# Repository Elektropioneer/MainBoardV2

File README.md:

# Electropioneer Main Board 
This repo is dedicated to developing the new Main Board for the Electropioneer team
## Software
We are using KiCAD to develop the PCB

## Protection from reverse current
We are using the simplest way to protect out circuits, a P-Channel MOSFET.
The MOSFET won't turn on when the voltage on the gate is above 0 (exact voltage defined in the datasheet)

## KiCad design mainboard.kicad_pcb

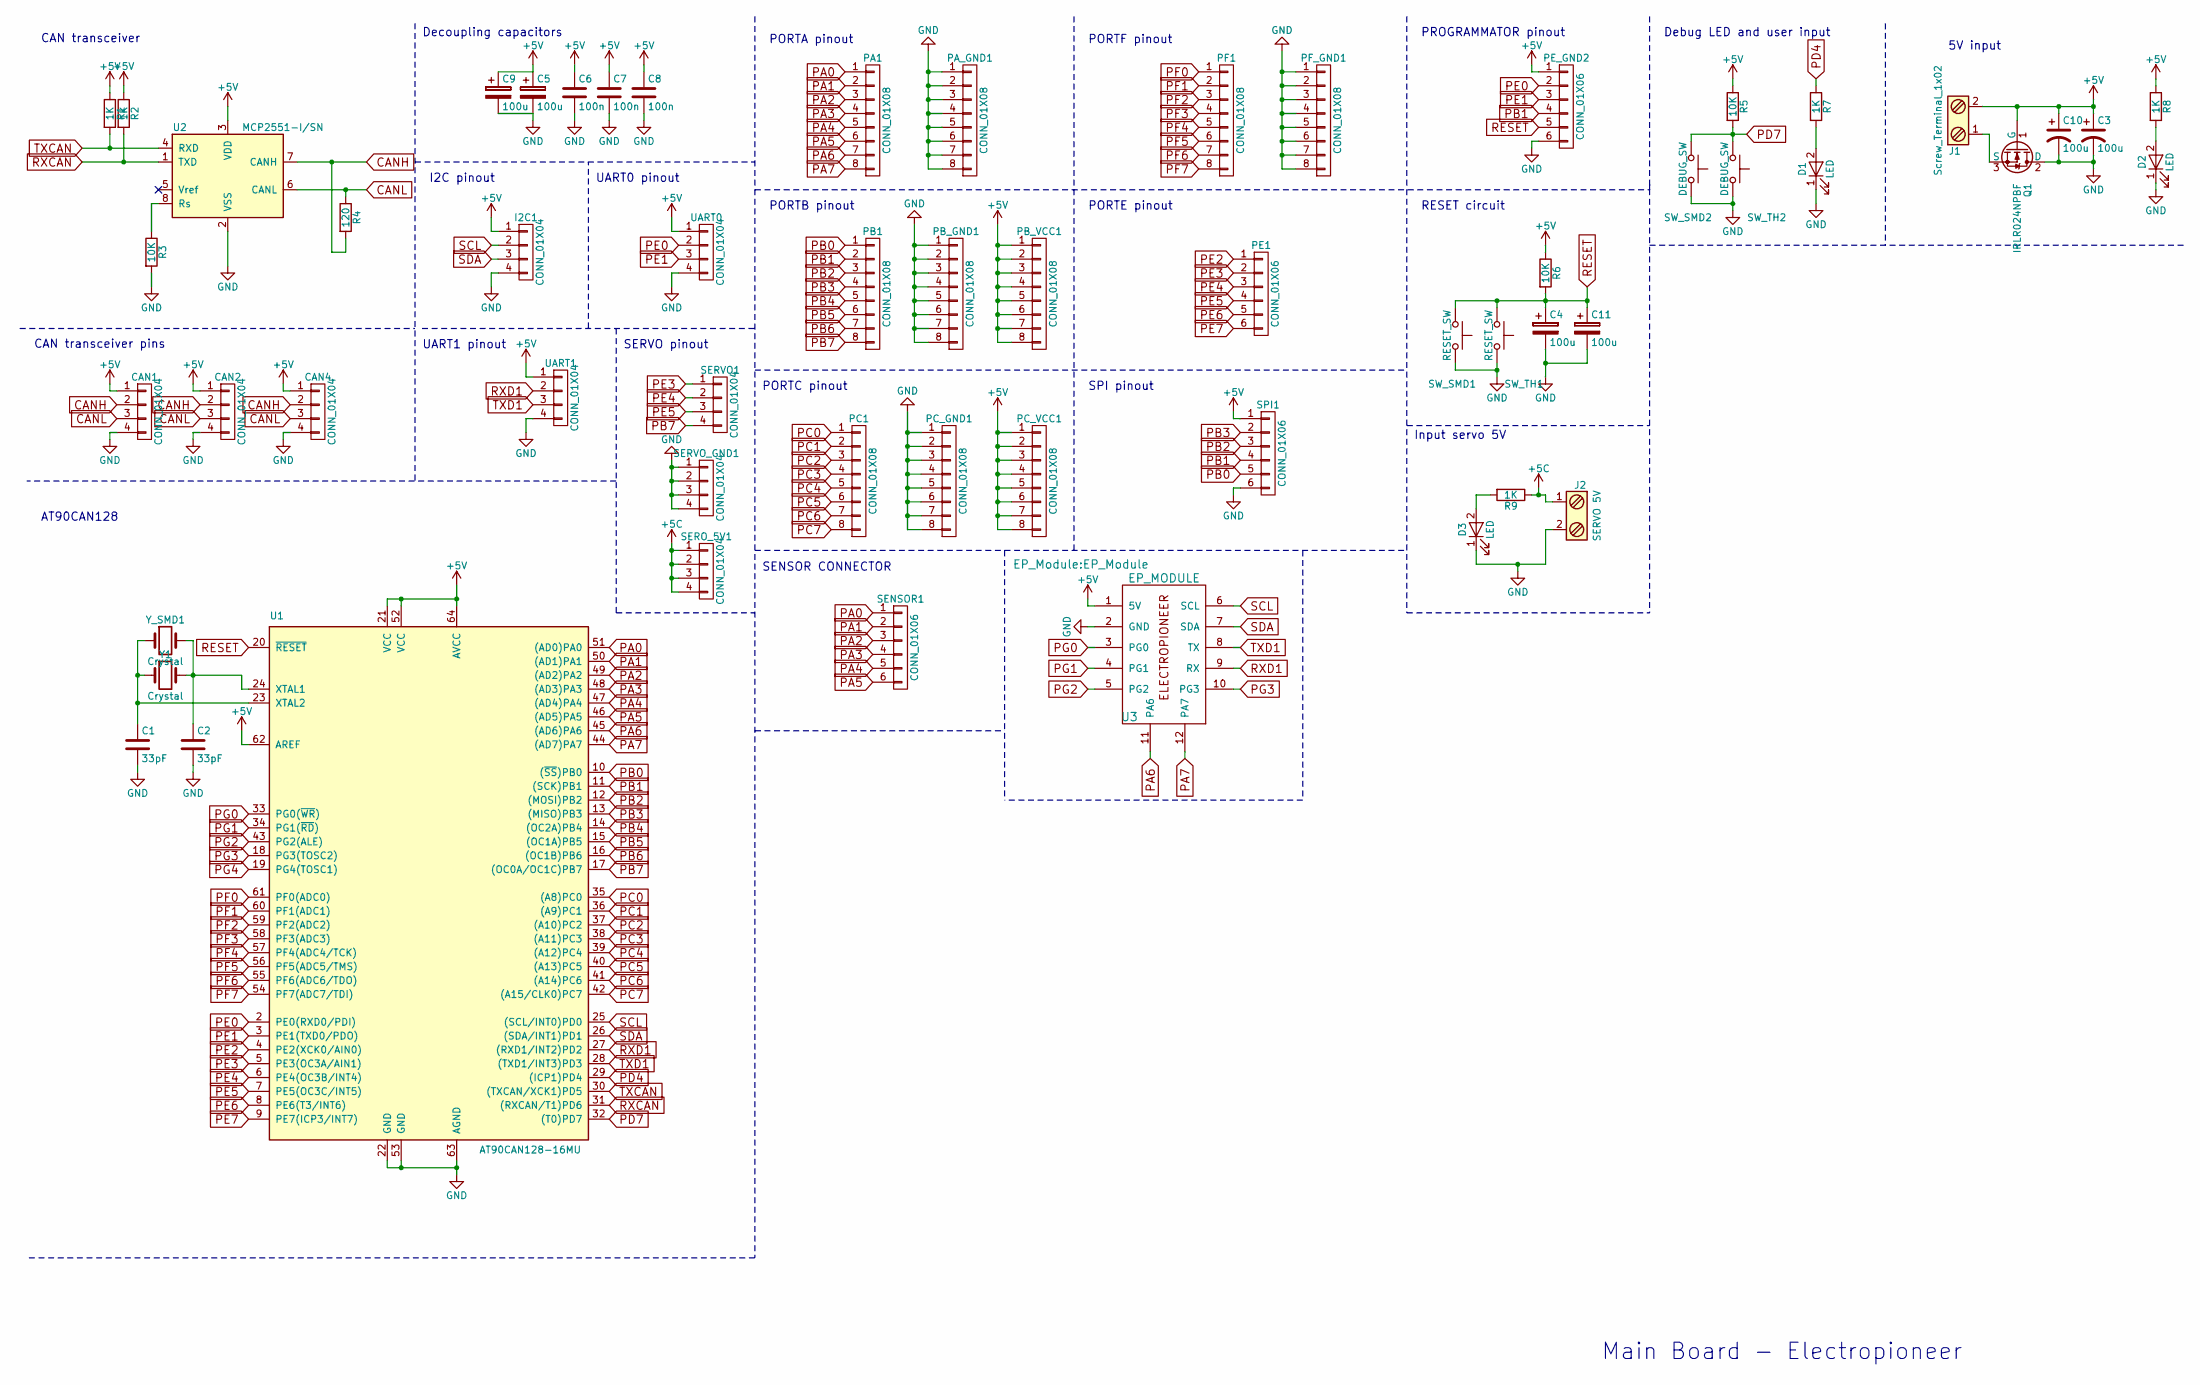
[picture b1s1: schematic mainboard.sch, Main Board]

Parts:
C1, C2: 33pF; C_0805
C3, C4, C5: 100u; CP_Elec_6.3x4.5
C6, C7, C8: 100n; C_0805
C9, C10, C11: 100u; CP_Radial_D7.5mm_P2.50mm
CAN1, CAN2, CAN4: CONN_01X04; Pin_Header_Straight_1x04_Pitch2.54mm
D1, D2, D3: LED; LED_0805
I2C1: CONN_01X04; Pin_Header_Straight_1x04_Pitch2.54mm
J1: Screw_Terminal_1x02; TerminalBlock_Pheonix_MPT-2.54mm_2pol
J2: SERVO 5V; TerminalBlock_Pheonix_MPT-2.54mm_2pol
PA1: CONN_01X08; Pin_Header_Straight_1x08_Pitch2.54mm
PA_GND1: CONN_01X08; Pin_Header_Straight_1x08_Pitch2.54mm
PB1: CONN_01X08; Pin_Header_Straight_1x08_Pitch2.54mm
PB_GND1: CONN_01X08; Pin_Header_Straight_1x08_Pitch2.54mm
PB_VCC1: CONN_01X08; Pin_Header_Straight_1x08_Pitch2.54mm
PC1: CONN_01X08; Pin_Header_Straight_1x08_Pitch2.54mm
PC_GND1: CONN_01X08; Pin_Header_Straight_1x08_Pitch2.54mm
PC_VCC1: CONN_01X08; Pin_Header_Straight_1x08_Pitch2.54mm
PE1: CONN_01X06; Pin_Header_Straight_1x06_Pitch2.54mm
PE_GND2: CONN_01X06; Pin_Header_Straight_1x06_Pitch2.54mm
PF1: CONN_01X08; Pin_Header_Straight_1x08_Pitch2.54mm
PF_GND1: CONN_01X08; Pin_Header_Straight_1x08_Pitch2.54mm
Q1: IRLR024NPBF; TO-252-2
R1, R2, R7, R8, R9: 1K; R_0805
R3, R5: 10K; R_0805
R4: 120; R_0805
R6: 10K; R_1206
SENSOR1: CONN_01X06; Pin_Header_Straight_1x06_Pitch2.54mm
SERO_5V1: CONN_01X04; Pin_Header_Straight_1x04_Pitch2.54mm
SERVO1: CONN_01X04; Pin_Header_Straight_1x04_Pitch2.54mm
SERVO_GND1: CONN_01X04; Pin_Header_Straight_1x04_Pitch2.54mm
SPI1: CONN_01X06; Pin_Header_Straight_1x06_Pitch2.54mm
SW_SMD1: RESET_SW; SW_DIP_x1_W7.62mm_Slide_Copal_CHS-B
SW_SMD2: DEBUG_SW; SW_DIP_x1_W7.62mm_Slide_Copal_CHS-B
SW_TH1: RESET_SW; SW_PUSH_6mm
SW_TH2: DEBUG_SW; SW_PUSH_6mm
U1: AT90CAN128-16MU; TQFP-64_14x14mm_Pitch0.8mm
U2: MCP2551-I/SN; SOIC-8_3.9x4.9mm_Pitch1.27mm
U3: EP_MODULE; EP_Module
UART0, UART1: CONN_01X04; Pin_Header_Straight_1x04_Pitch2.54mm
Y1: Crystal; Crystal_HC18-U_Vertical
Y_SMD1: Crystal; Crystal_SMD_HC49-SD

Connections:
+5C: J2.1, R9.1, SERO_5V1.1, SERO_5V1.2, SERO_5V1.3, SERO_5V1.4
+5V: C3.1, C5.1, C6.1, C7.1, C8.1, C9.1, C10.1, CAN1.1, CAN2.1, CAN4.1, I2C1.1, J1.2, PB_VCC1.1, PB_VCC1.2, PB_VCC1.3, PB_VCC1.4, PB_VCC1.5, PB_VCC1.6, PB_VCC1.7, PB_VCC1.8, PC_VCC1.1, PC_VCC1.2, PC_VCC1.3, PC_VCC1.4, PC_VCC1.5, PC_VCC1.6, PC_VCC1.7, PC_VCC1.8, PE_GND2.1, Q1.1 (G), R1.1, R2.1, R5.1, R6.1, R8.1, SPI1.1, U1.21 (VCC), U1.52 (VCC), U1.62 (AREF), U1.64 (AVCC), U2.3 (VDD), U3.1 (5V), UART0.1, UART1.1
CANH: CAN1.2, CAN2.2, CAN4.2, R4.2, U2.7 (CANH)
CANL: CAN1.3, CAN2.3, CAN4.3, R4.1, U2.6 (CANL)
GND: C1.2, C2.2, C3.2, C4.2, C5.2, C6.2, C7.2, C8.2, C9.2, C10.2, C11.2, CAN1.4, CAN2.4, CAN4.4, D1.1 (K), D2.1 (K), D3.1 (K), I2C1.4, J2.2, PA_GND1.1, PA_GND1.2, PA_GND1.3, PA_GND1.4, PA_GND1.5, PA_GND1.6, PA_GND1.7, PA_GND1.8, PB_GND1.1, PB_GND1.2, PB_GND1.3, PB_GND1.4, PB_GND1.5, PB_GND1.6, PB_GND1.7, PB_GND1.8, PC_GND1.1, PC_GND1.2, PC_GND1.3, PC_GND1.4, PC_GND1.5, PC_GND1.6, PC_GND1.7, PC_GND1.8, PE_GND2.6, PF_GND1.1, PF_GND1.2, PF_GND1.3, PF_GND1.4, PF_GND1.5, PF_GND1.6, PF_GND1.7, PF_GND1.8, Q1.2 (D), R3.2, SERVO_GND1.1, SERVO_GND1.2, SERVO_GND1.3, SERVO_GND1.4, SPI1.6, SW_SMD1.2, SW_SMD2.2, SW_TH1.2, SW_TH2.2, U1.22 (GND), U1.53 (GND), U1.63 (AGND), U2.2 (VSS), U3.2 (GND), UART0.4, UART1.4
unnamed: C1.1, U1.23 (XTAL2), Y1.1, Y_SMD1.1
unnamed: C2.1, U1.24 (XTAL1), Y1.2, Y_SMD1.2
unnamed: D1.2 (A), R7.2
unnamed: D2.2 (A), R8.2
unnamed: D3.2 (A), R9.2
unnamed: J1.1, Q1.3 (S)
unnamed: R3.1, U2.8 (Rs)
PA0: PA1.1, SENSOR1.1, U1.51 ((AD0)PA0)
PA1: PA1.2, SENSOR1.2, U1.50 ((AD1)PA1)
PA2: PA1.3, SENSOR1.3, U1.49 ((AD2)PA2)
PA3: PA1.4, SENSOR1.4, U1.48 ((AD3)PA3)
PA4: PA1.5, SENSOR1.5, U1.47 ((AD4)PA4)
PA5: PA1.6, SENSOR1.6, U1.46 ((AD5)PA5)
PA6: PA1.7, U1.45 ((AD6)PA6), U3.11 (PA6)
PA7: PA1.8, U1.44 ((AD7)PA7), U3.12 (PA7)
PB0: PB1.1, SPI1.5, U1.10 ((~SS~)PB0)
PB1: PB1.2, PE_GND2.4, SPI1.4, U1.11 ((SCK)PB1)
PB2: PB1.3, SPI1.3, U1.12 ((MOSI)PB2)
PB3: PB1.4, SPI1.2, U1.13 ((MISO)PB3)
PB4: PB1.5, U1.14 ((OC2A)PB4)
PB5: PB1.6, U1.15 ((OC1A)PB5)
PB6: PB1.7, U1.16 ((OC1B)PB6)
PB7: PB1.8, SERVO1.4, U1.17 ((OC0A/OC1C)PB7)
PC0: PC1.1, U1.35 ((A8)PC0)
PC1: PC1.2, U1.36 ((A9)PC1)
PC2: PC1.3, U1.37 ((A10)PC2)
PC3: PC1.4, U1.38 ((A11)PC3)
PC4: PC1.5, U1.39 ((A12)PC4)
PC5: PC1.6, U1.40 ((A13)PC5)
PC6: PC1.7, U1.41 ((A14)PC6)
PC7: PC1.8, U1.42 ((A15/CLK0)PC7)
PD4: R7.1, U1.29 ((ICP1)PD4)
PD7: R5.2, SW_SMD2.1, SW_TH2.1, U1.32 ((T0)PD7)
PE0: PE_GND2.2, U1.2 (PE0(RXD0/PDI)), UART0.2
PE1: PE_GND2.3, U1.3 (PE1(TXD0/PDO)), UART0.3
PE2: PE1.1, U1.4 (PE2(XCK0/AIN0))
PE3: PE1.2, SERVO1.1, U1.5 (PE3(OC3A/AIN1))
PE4: PE1.3, SERVO1.2, U1.6 (PE4(OC3B/INT4))
PE5: PE1.4, SERVO1.3, U1.7 (PE5(OC3C/INT5))
PE6: PE1.5, U1.8 (PE6(T3/INT6))
PE7: PE1.6, U1.9 (PE7(ICP3/INT7))
PF0: PF1.1, U1.61 (PF0(ADC0))
PF1: PF1.2, U1.60 (PF1(ADC1))
PF2: PF1.3, U1.59 (PF2(ADC2))
PF3: PF1.4, U1.58 (PF3(ADC3))
PF4: PF1.5, U1.57 (PF4(ADC4/TCK))
PF5: PF1.6, U1.56 (PF5(ADC5/TMS))
PF6: PF1.7, U1.55 (PF6(ADC6/TDO))
PF7: PF1.8, U1.54 (PF7(ADC7/TDI))
PG0: U1.33 (PG0(~WR~)), U3.3 (PG0)
PG1: U1.34 (PG1(~RD~)), U3.4 (PG1)
PG2: U1.43 (PG2(ALE)), U3.5 (PG2)
PG3: U1.18 (PG3(TOSC2)), U3.10 (PG3)
RESET: C4.1, C11.1, PE_GND2.5, R6.2, SW_SMD1.1, SW_TH1.1, U1.20 (~RESET)
RXCAN: R2.2, U1.31 ((RXCAN/T1)PD6), U2.1 (TXD)
RXD1: U1.27 ((RXD1/INT2)PD2), U3.9 (RX), UART1.2
SCL: I2C1.2, U1.25 ((SCL/INT0)PD0), U3.6 (SCL)
SDA: I2C1.3, U1.26 ((SDA/INT1)PD1), U3.7 (SDA)
TXCAN: R1.2, U1.30 ((TXCAN/XCK1)PD5), U2.4 (RXD)
TXD1: U1.28 ((TXD1/INT3)PD3), U3.8 (TX), UART1.3

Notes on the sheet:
CAN transceiver
5V input
Debug LED and user input
CAN transceiver pins
I2C pinout
UART0 pinout
UART1 pinout
SERVO pinout
PORTA pinout
PORTB pinout
PORTC pinout
SPI pinout
PORTE pinout
PORTF pinout
PROGRAMMATOR pinout
RESET circuit
Decoupling capacitors
AT90CAN128
SENSOR CONNECTOR
Input servo 5V
Main Board - Electropioneer

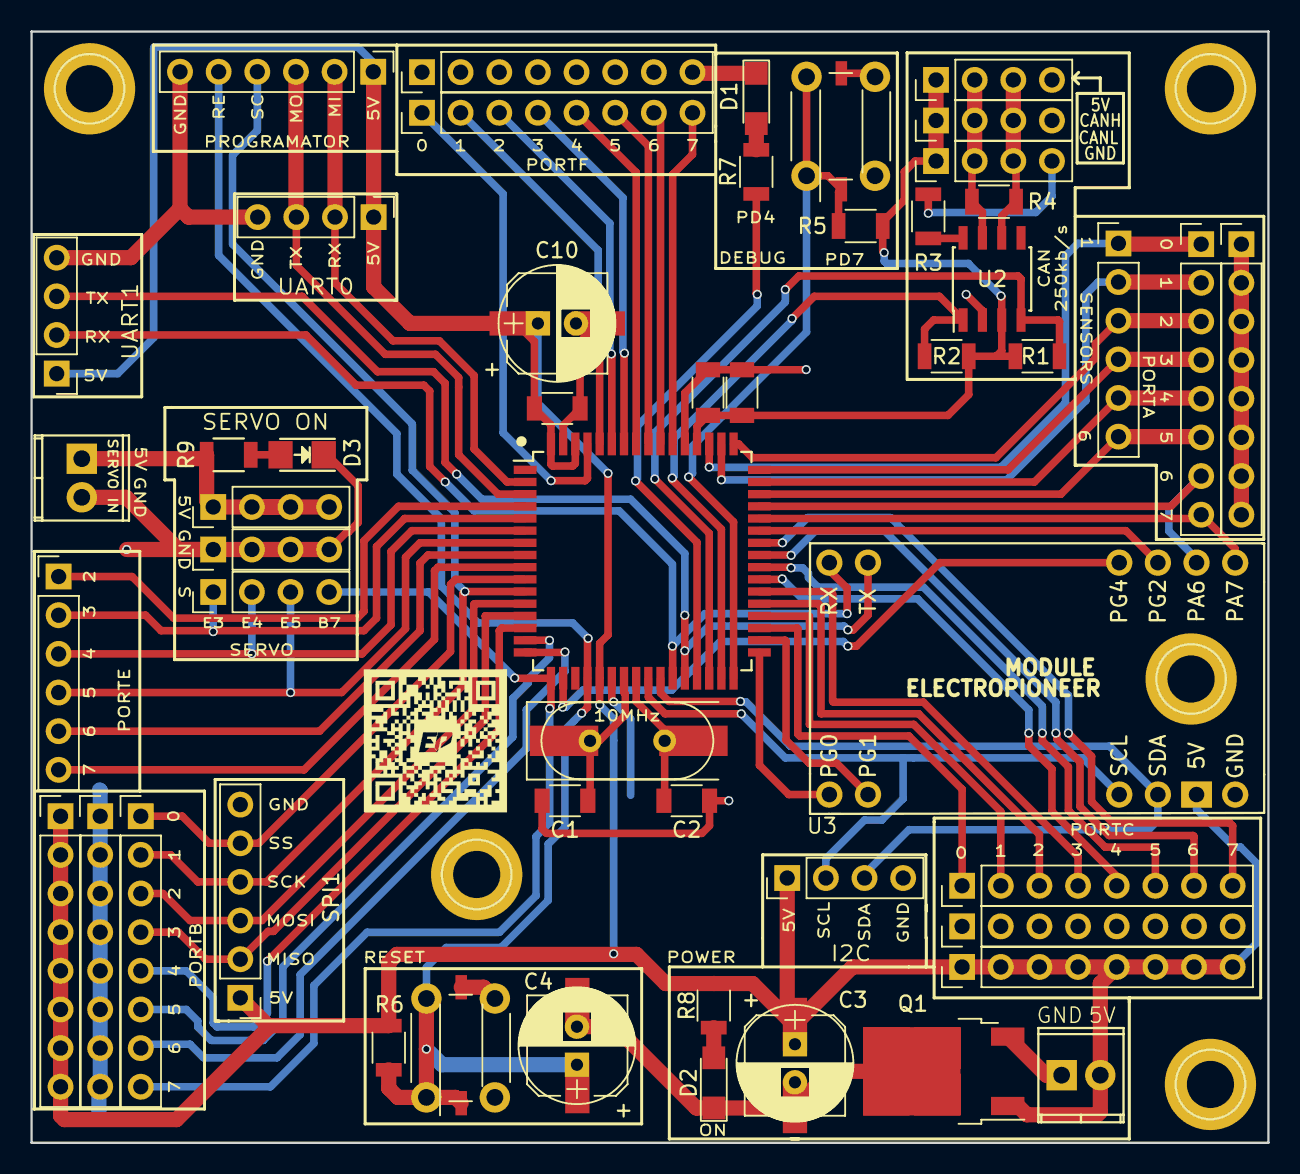
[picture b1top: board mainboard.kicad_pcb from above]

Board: 2 copper layers, 81.3 x 73.0 mm, 58 parts (0 on the bottom side), 65 nets.

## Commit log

2017-07-02 Starting to get its form but not there yet
2017-07-03 Added new smd components, still need protection circuit and routing
2017-07-03 Added new smd components, still need protection circuit and routing V2
2017-07-05 Added protection, made board design and routing
2017-07-05 Removed some trases
2017-07-05 Removed some trases v2
2017-07-05 Removed some trases v3
2017-07-07 Added images
2017-07-07 Update README.md
    Added images...
2017-07-07 Update README.md
    Changes to readme
2017-07-07 Update README.md
    Added text
2017-07-20 Modified mosfet protection to smd
2017-07-20 moved
2017-07-20 Updated readme with new file paths and mosfet
2017-07-20 Updated the url for mosfet
2017-09-03 Did some power things
2017-09-03 Added the zone
2017-10-01 New idea around servo power and new mosfet version for protection
2017-10-01 Added mosfet and servo
2017-10-01 Added some bottom paste
2017-10-18 Modified alot of stuff, added module and power for servo
2017-10-18 modified the reamde for dev
2017-10-18 Modifyed positions around U3
2017-10-18 New screen
2017-10-18 Small modif
2017-10-18 Small modifs, but important
2017-10-22 Changed some footprints from 0603 t 0805
2017-10-28 Final touches
2017-10-28 Added test DXF
2017-11-06 Added output files
2017-11-06 Wont export, but it exports .cad
2017-11-08 Added new wrl file
2017-11-09 Added new graphics
2017-11-09 Modified the readme a bit
2018-02-10 Added EP_Module to glavna
